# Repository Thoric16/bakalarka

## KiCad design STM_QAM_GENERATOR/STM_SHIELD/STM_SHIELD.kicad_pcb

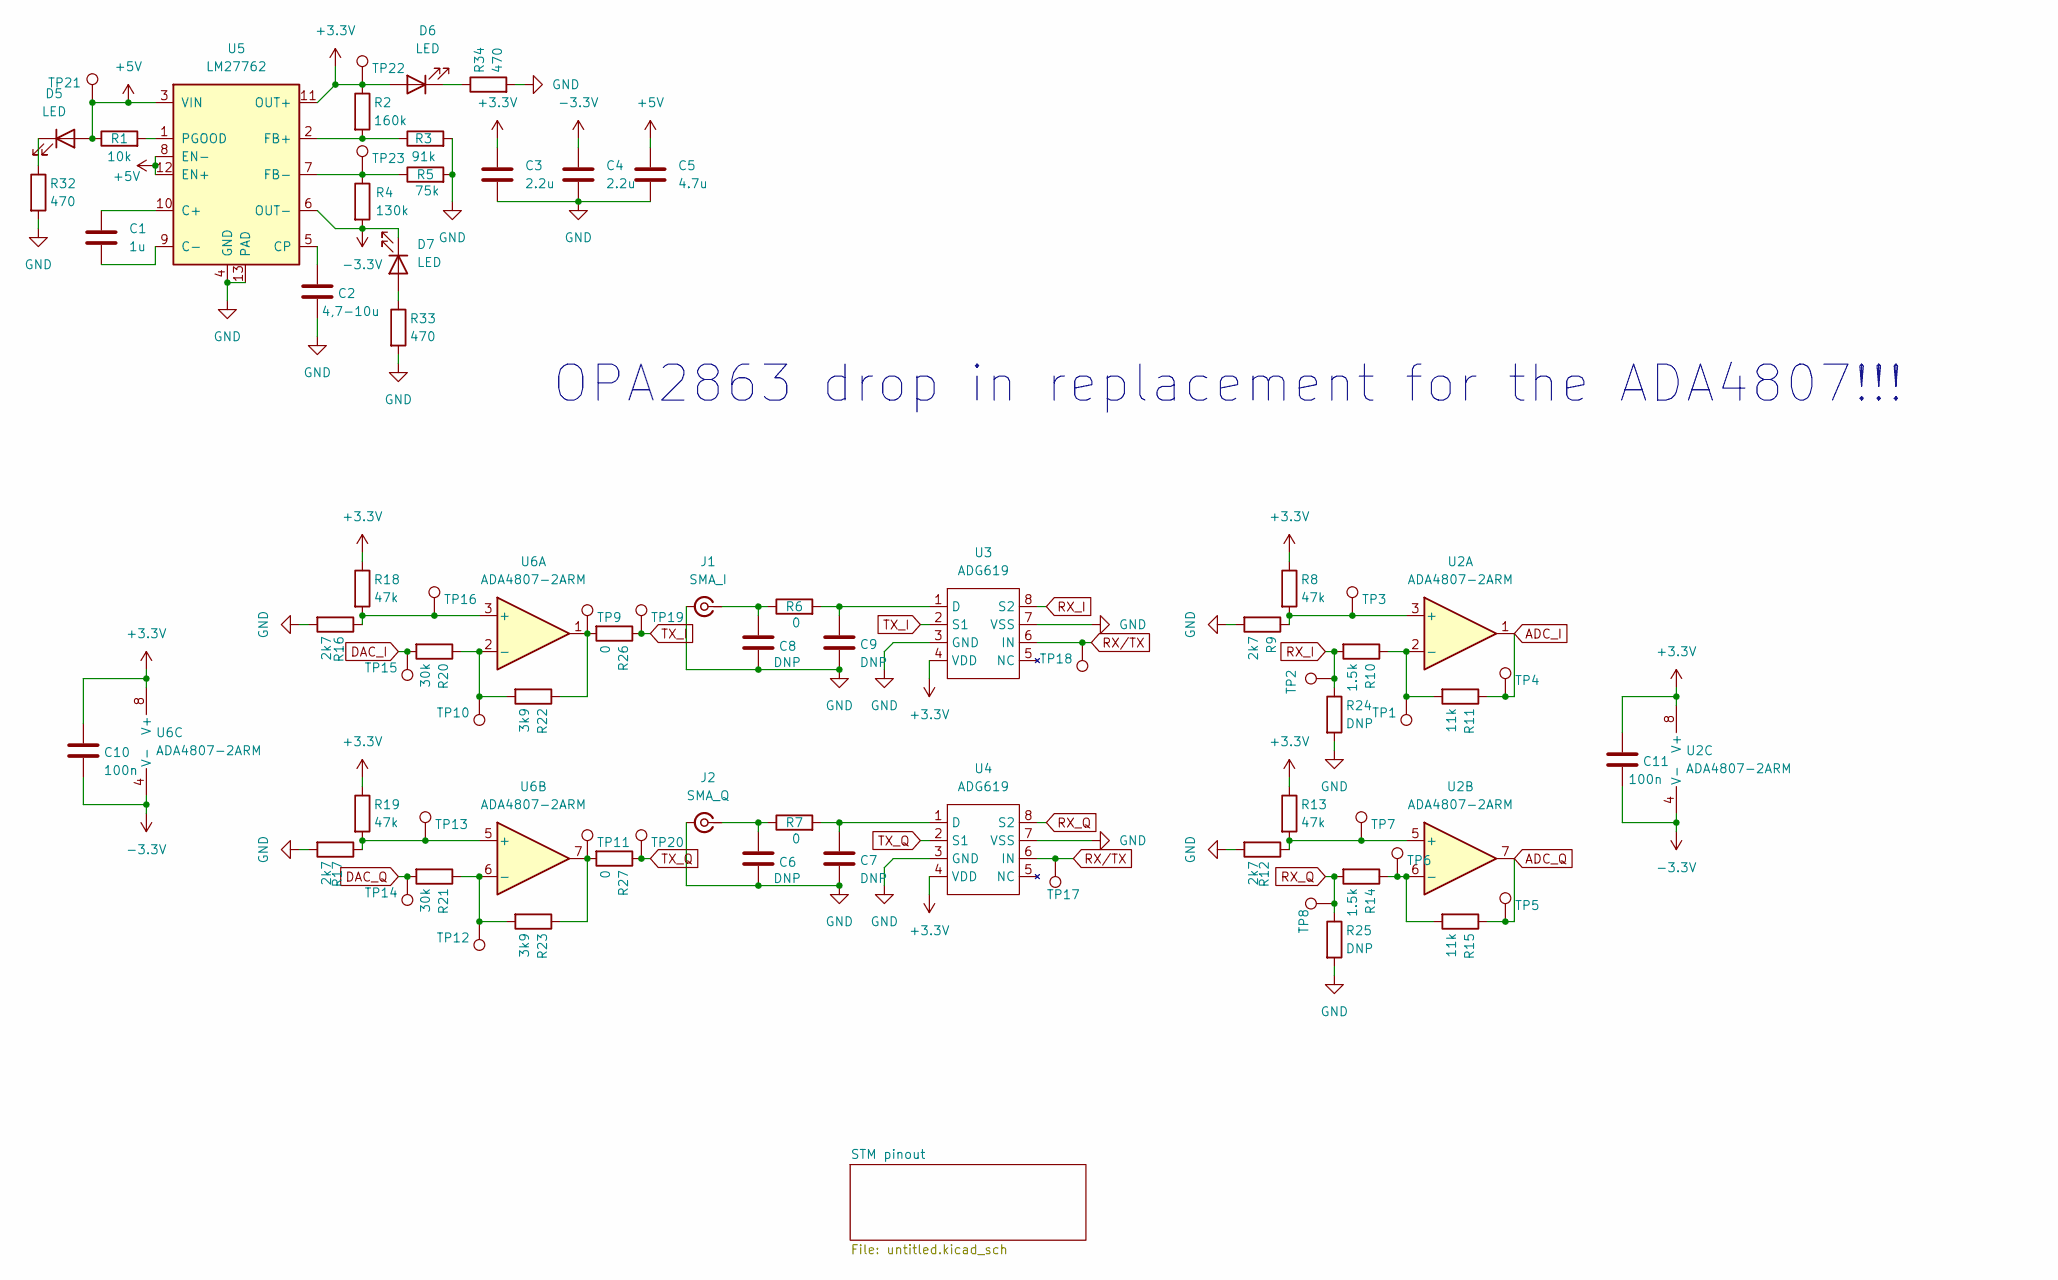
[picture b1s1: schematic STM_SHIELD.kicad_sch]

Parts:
C1: 1u; C_0603_1608Metric_Pad1.08x0.95mm_HandSolder
C2: 4,7-10u; C_0603_1608Metric_Pad1.08x0.95mm_HandSolder
C3, C4: 2.2u; C_0603_1608Metric_Pad1.08x0.95mm_HandSolder
C5: 4.7u; C_0603_1608Metric_Pad1.08x0.95mm_HandSolder
C6, C7, C8, C9: DNP; C_0603_1608Metric_Pad1.08x0.95mm_HandSolder
C10, C11: 100n; C_0603_1608Metric_Pad1.08x0.95mm_HandSolder
D5, D6, D7: LED; LED_0603_1608Metric_Pad1.05x0.95mm_HandSolder
J1: SMA_I; SMA_Samtec_SMA-J-P-H-ST-EM1_EdgeMount
J2: SMA_Q; SMA_Samtec_SMA-J-P-H-ST-EM1_EdgeMount
R1: 10k; R_0603_1608Metric_Pad0.98x0.95mm_HandSolder
R2: 160k; R_0603_1608Metric_Pad0.98x0.95mm_HandSolder
R3: 91k; R_0603_1608Metric_Pad0.98x0.95mm_HandSolder
R4: 130k; R_0603_1608Metric_Pad0.98x0.95mm_HandSolder
R5: 75k; R_0603_1608Metric_Pad0.98x0.95mm_HandSolder
R6, R7, R26, R27: 0; R_0603_1608Metric_Pad0.98x0.95mm_HandSolder
R8, R13, R18, R19: 47k; R_0603_1608Metric_Pad0.98x0.95mm_HandSolder
R9, R12, R16, R17: 2k7; R_0603_1608Metric_Pad0.98x0.95mm_HandSolder
R10, R14: 1.5k; R_0603_1608Metric_Pad0.98x0.95mm_HandSolder
R11, R15: 11k; R_0603_1608Metric_Pad0.98x0.95mm_HandSolder
R20, R21: 30k; R_0603_1608Metric_Pad0.98x0.95mm_HandSolder
R22, R23: 3k9; R_0603_1608Metric_Pad0.98x0.95mm_HandSolder
R24, R25: DNP; R_0603_1608Metric_Pad0.98x0.95mm_HandSolder
R32, R33, R34: 470; R_0603_1608Metric_Pad0.98x0.95mm_HandSolder
TP1, TP2, TP3, TP4, TP5, TP6, TP7, TP8, TP9, TP10, TP11, TP12, TP13, TP14, TP15, TP16, TP17, TP18, TP19, TP20, TP21, TP22, TP23: TestPoint; TestPoint_Pad_D1.0mm
U2, U6: ADA4807-2ARM; MSOP-8_3x3mm_P0.65mm
U3, U4: ADG619; MSOP-8_3x3mm_P0.65mm
U5: LM27762; WSON-12-1EP_3x2mm_P0.5mm_EP1x2.65_ThermalVias

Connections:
+3.3V: C3.2, C10.2, C11.2, D6.2 (A), R2.1, R8.1, R13.1, R18.1, R19.1, TP22.1, U2.8 (V+), U3.4 (VDD), U4.4 (VDD), U5.11 (OUT+), U6.8 (V+)
+5V: C5.2, D5.2 (A), R1.1, TP21.1, U5.3 (VIN), U5.8 (EN-), U5.12 (EN+); also elsewhere on the board
-3.3V: C4.2, C10.1, C11.1, D7.1 (K), R4.2, U2.4 (V-), U5.6 (OUT-), U6.4 (V-)
ADC_I: R11.1, TP4.1, U2.1; also elsewhere on the board
ADC_Q: R15.1, TP5.1, U2.7; also elsewhere on the board
DAC_I: R20.2, TP15.1; also elsewhere on the board
DAC_Q: R21.2, TP14.1; also elsewhere on the board
GND: C2.1, C3.1, C4.1, C5.1, C6.1, C7.1, C8.1, C9.1, J1.2 (Ext), J2.2 (Ext), R3.2, R5.2, R9.2, R12.2, R16.2, R17.2, R24.2, R25.2, R32.2, R33.2, R34.2, U3.3 (GND), U3.7 (VSS), U4.3 (GND), U4.7 (VSS), U5.4 (GND), U5.13 (PAD); also elsewhere on the board
unnamed: D5.1 (K), R32.1
unnamed: D6.1 (K), R34.1
unnamed: D7.2 (A), R33.1
unnamed: C8.2, J1.1 (In), R6.1
unnamed: C6.2, J2.1 (In), R7.1
unnamed: R22.1, R26.2, TP9.1, U6.1
unnamed: R23.1, R27.2, TP11.1, U6.7
unnamed: R8.2, R9.1, TP3.1, U2.3 (+)
unnamed: R10.1, R11.2, TP1.1, U2.2 (-)
unnamed: R12.1, R13.2, TP7.1, U2.5 (+)
unnamed: R14.1, R15.2, TP6.1, U2.6 (-)
unnamed: C9.2, R6.2, U3.1 (D)
unnamed: C7.2, R7.2, U4.1 (D)
unnamed: C1.2, U5.10 (C+)
unnamed: C1.1, U5.9 (C-)
unnamed: C2.2, U5.5 (CP)
unnamed: R2.2, R3.1, U5.2 (FB+)
unnamed: R4.1, R5.1, TP23.1, U5.7 (FB-)
unnamed: R1.2, U5.1 (PGOOD)
unnamed: R16.1, R18.2, TP16.1, U6.3 (+)
unnamed: R20.1, R22.2, TP10.1, U6.2 (-)
unnamed: R17.1, R19.2, TP13.1, U6.5 (+)
unnamed: R21.1, R23.2, TP12.1, U6.6 (-)
RX_I: R10.2, R24.1, TP2.1, U3.8 (S2)
RX_Q: R14.2, R25.1, TP8.1, U4.8 (S2)
RX/TX: TP17.1, TP18.1, U3.6 (IN), U4.6 (IN); also elsewhere on the board
TX_I: R26.1, TP19.1, U3.2 (S1)
TX_Q: R27.1, TP20.1, U4.2 (S1)

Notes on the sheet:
OPA2863 drop in replacement for the ADA4807!!!

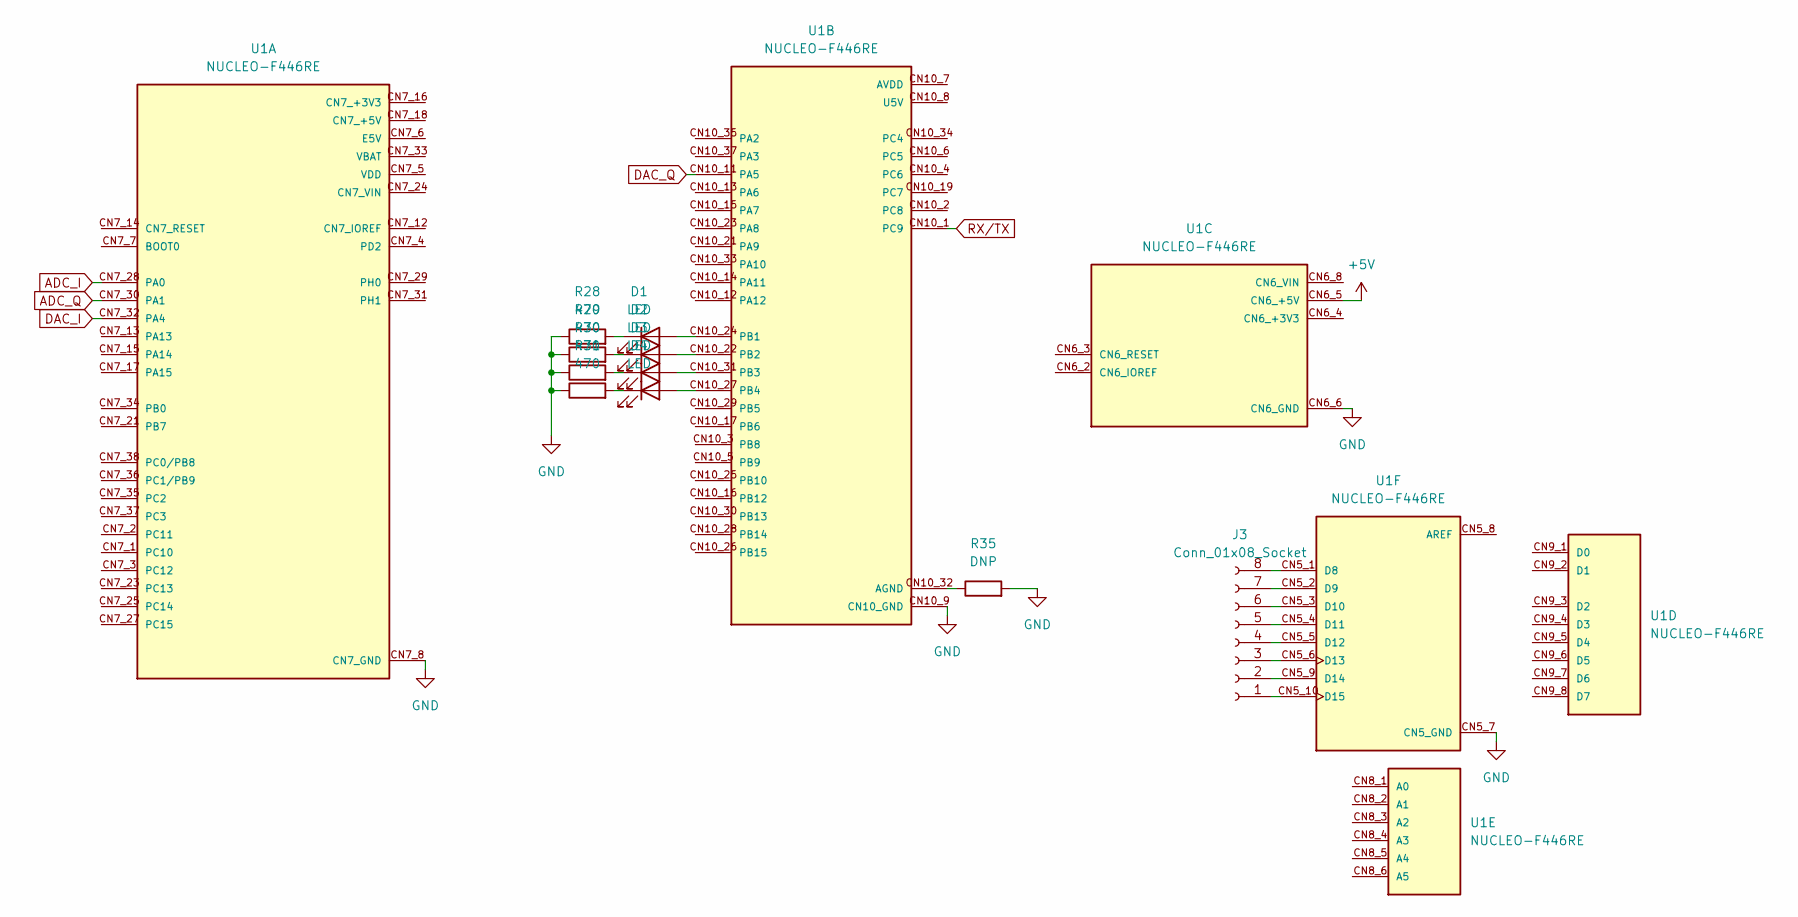
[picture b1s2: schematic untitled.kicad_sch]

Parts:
D1, D2, D3, D4: LED; LED_0603_1608Metric_Pad1.05x0.95mm_HandSolder
J3: Conn_01x08_Socket; PinSocket_1x08_P2.54mm_Vertical
R28, R29, R30, R31: 470; R_0603_1608Metric_Pad0.98x0.95mm_HandSolder
R35: DNP; R_0603_1608Metric_Pad0.98x0.95mm_HandSolder
U1: NUCLEO-F446RE; MODULE_NUCLEO-F446RE; PARTREV 13

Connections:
+5V: U1.CN6_5 (CN6_+5V); also elsewhere on the board
ADC_I: U1.CN7_28 (PA0); also elsewhere on the board
ADC_Q: U1.CN7_30 (PA1); also elsewhere on the board
DAC_I: U1.CN7_32 (PA4); also elsewhere on the board
DAC_Q: U1.CN10_11 (PA5); also elsewhere on the board
GND: R28.1, R29.1, R30.1, R31.1, R35.2, U1.CN5_7 (CN5_GND), U1.CN6_6 (CN6_GND), U1.CN6_7 (CN6_GND), U1.CN7_8 (CN7_GND), U1.CN7_19 (CN7_GND), U1.CN7_20 (CN7_GND), U1.CN7_22 (CN7_GND), U1.CN10_9 (CN10_GND), U1.CN10_20 (CN10_GND); also elsewhere on the board
unnamed: D1.2 (A), U1.CN10_24 (PB1)
unnamed: D1.1 (K), R28.2
unnamed: D2.2 (A), U1.CN10_22 (PB2)
unnamed: D2.1 (K), R29.2
unnamed: D3.2 (A), U1.CN10_31 (PB3)
unnamed: D3.1 (K), R30.2
unnamed: D4.2 (A), U1.CN10_27 (PB4)
unnamed: D4.1 (K), R31.2
unnamed: J3.1, U1.CN5_10 (D15)
unnamed: J3.2, U1.CN5_9 (D14)
unnamed: J3.3, U1.CN5_6 (D13)
unnamed: J3.4, U1.CN5_5 (D12)
unnamed: J3.5, U1.CN5_4 (D11)
unnamed: J3.6, U1.CN5_3 (D10)
unnamed: J3.7, U1.CN5_2 (D9)
unnamed: J3.8, U1.CN5_1 (D8)
unnamed: R35.1, U1.CN10_32 (AGND)
RX/TX: U1.CN10_1 (PC9); also elsewhere on the board

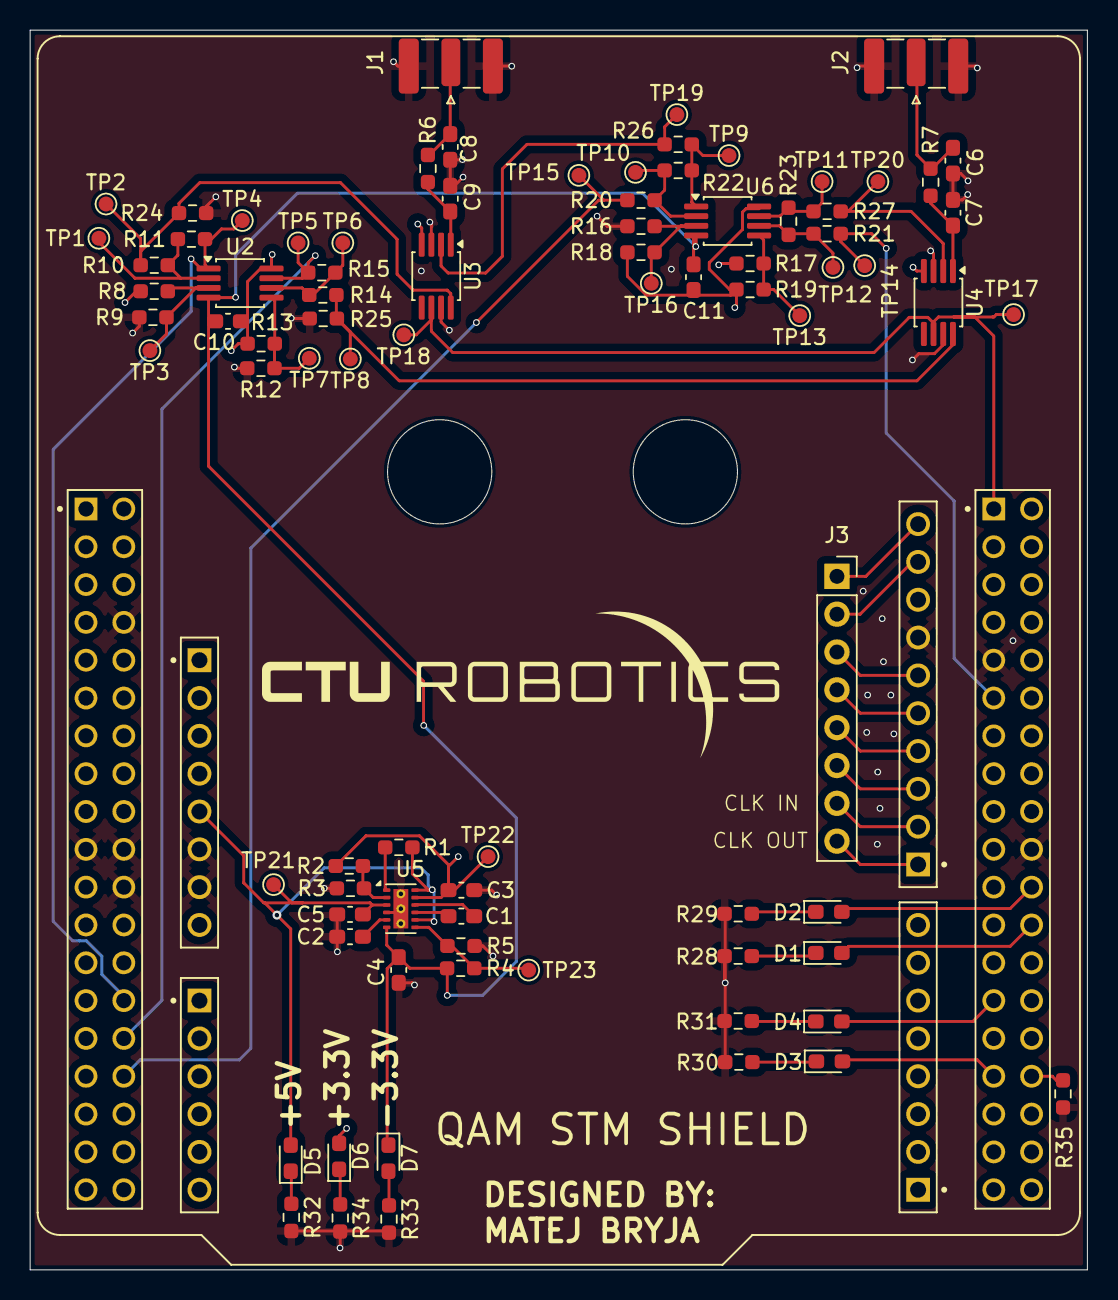
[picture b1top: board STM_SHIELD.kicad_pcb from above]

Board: 4 copper layers, 71.0 x 83.2 mm, 85 parts (0 on the bottom side), 53 nets.

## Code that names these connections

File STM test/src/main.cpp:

#include <Arduino.h>
#include <HardwareTimer.h>

constexpr uint8_t DAC_I_PIN = PA4;
constexpr uint8_t DAC_Q_PIN = PA5;
constexpr uint8_t ADC_I_PIN = PA0;
constexpr uint8_t ADC_Q_PIN = PA1;
constexpr uint8_t TX_CLOCK_PIN = D8;
constexpr uint8_t RX_CLOCK_PIN = D9;
constexpr uint8_t TX_MODE_PIN = PB1;
constexpr uint8_t RX_MODE_PIN = PB2;
constexpr uint8_t USER_BUTTON_PIN = PC13;
constexpr uint16_t DAC_MAX = 4095;
constexpr uint32_t SYMBOL_PERIOD_US = 1000;
constexpr uint32_t CLOCK_FREQUENCY_HZ = 1000000UL / SYMBOL_PERIOD_US;
constexpr uint32_t BUTTON_DEBOUNCE_MS = 50;
constexpr uint32_t LONG_PRESS_MS = 1500;
constexpr float ADC_REFERENCE_VOLTAGE = 3.3f;
constexpr uint8_t RX_PACKET_HEADER = 0xA5;
constexpr uint16_t RX_BUFFER_SIZE = 512;

struct Modulation {
  const char *name;
  uint16_t order;
  uint8_t bitsPerAxis;
};

const Modulation modulations[] = {
  {"QPSK", 4, 1},
  {"16-QAM", 16, 2},
  {"64-QAM", 64, 3},
  {"256-QAM", 256, 4},
  {"1024-QAM", 1024, 5},
  {"4096-QAM", 4096, 6}
};

constexpr size_t MODULATION_COUNT = sizeof(modulations) / sizeof(modulations[0]);
size_t modulationIndex = 0;
uint16_t symbolIndex = 0;
bool stableButtonState = HIGH;
bool candidateButtonState = HIGH;
uint32_t buttonStateChangedAt = 0;
uint32_t buttonPressStart = 0;
bool longPressHandled = false;
bool receiverMode = false;
struct RxSample {
  uint16_t i;
  uint16_t q;
};

volatile RxSample rxBuffer[RX_BUFFER_SIZE];
volatile uint16_t rxBufferHead = 0;
volatile uint16_t rxBufferTail = 0;
volatile uint32_t rxDroppedSamples = 0;
HardwareTimer *txClockTimer = nullptr;

uint16_t axisLevel(uint16_t axisIndex, uint8_t bitsPerAxis) {
  const uint16_t axisLevels = 1U << bitsPerAxis;
  if (axisLevels == 1) {
    return DAC_MAX / 2;
  }
  return static_cast<uint16_t>((static_cast<uint32_t>(axisIndex) * DAC_MAX) / (axisLevels - 1));
}

void printModulationInfo() {
  const Modulation &modulation = modulations[modulationIndex];
  Serial.println();
  Serial.print("--- ");
  Serial.print(receiverMode ? "RX" : "TX");
  Serial.println(" mode ---");
  Serial.print("Current modulation: ");
  Serial.println(modulation.name);
  Serial.print("States: ");
  Serial.println(modulation.order);
  Serial.print("Bits per symbol: ");
  Serial.println(2 * modulation.bitsPerAxis);
  Serial.println("DAC pins: I=PA4, Q=PA5, range=0..4095");
  Serial.println("ADC pins: I=PA0, Q=PA1");
  Serial.println("Clock pins: TX=D8, RX=D9");
  Serial.println("RX samples ADC values on each rising clock edge.");
  Serial.println("Short press: next modulation. Hold 1.5 s: toggle TX/RX.");
}

void receiveClockEdge() {
  const uint16_t nextHead = (rxBufferHead + 1) % RX_BUFFER_SIZE;
  if (nextHead == rxBufferTail) {
    rxDroppedSamples++;
    return;
  }

  rxBuffer[rxBufferHead].i = analogRead(ADC_I_PIN);
  rxBuffer[rxBufferHead].q = analogRead(ADC_Q_PIN);
  rxBufferHead = nextHead;
}

void setMode(bool newReceiverMode) {
  receiverMode = newReceiverMode;
  symbolIndex = 0;
  digitalWrite(TX_MODE_PIN, receiverMode ? LOW : HIGH);
  digitalWrite(RX_MODE_PIN, receiverMode ? HIGH : LOW);
  noInterrupts();
  rxBufferHead = 0;
  rxBufferTail = 0;
  rxDroppedSamples = 0;
  interrupts();

  if (receiverMode) {
    txClockTimer->pause();
    detachInterrupt(digitalPinToInterrupt(RX_CLOCK_PIN));
    pinMode(TX_CLOCK_PIN, INPUT);
    pinMode(RX_CLOCK_PIN, INPUT);
    attachInterrupt(digitalPinToInterrupt(RX_CLOCK_PIN), receiveClockEdge, RISING);
  } else {
    detachInterrupt(digitalPinToInterrupt(RX_CLOCK_PIN));
    pinMode(RX_CLOCK_PIN, INPUT);
    txClockTimer->setMode(1, TIMER_OUTPUT_COMPARE_PWM1, TX_CLOCK_PIN);
    txClockTimer->setCount(0);
    txClockTimer->resume();
  }

  printModulationInfo();
}

void streamReceivedSamples() {
  uint8_t streamedSamples = 0;
  while (streamedSamples < 32) {
    uint16_t currentI;
    uint16_t currentQ;

    noInterrupts();
    if (rxBufferTail == rxBufferHead) {
      interrupts();
      return;
    }
    currentI = rxBuffer[rxBufferTail].i;
    streamedSamples++;
    currentQ = rxBuffer[rxBufferTail].q;
    rxBufferTail = (rxBufferTail + 1) % RX_BUFFER_SIZE;
    interrupts();

    const uint8_t packet[] = {
        RX_PACKET_HEADER,
        static_cast<uint8_t>(currentI & 0xFF),
        static_cast<uint8_t>(currentI >> 8),
        static_cast<uint8_t>(currentQ & 0xFF),
        static_cast<uint8_t>(currentQ >> 8)};
    Serial.write(packet, sizeof(packet));
  }
}

void processSerialCommands() {
  static char command[16];
  static uint8_t commandLength = 0;

  while (Serial.available() > 0) {
    const char character = static_cast<char>(Serial.read());
    if (character == '\n' || character == '\r') {
      command[commandLength] = '\0';
      if (strcmp(command, "RX") == 0) {
        setMode(true);
      } else if (strcmp(command, "TX") == 0) {
        setMode(false);
      } else if (strcmp(command, "NEXT") == 0 && !receiverMode) {
        modulationIndex = (modulationIndex + 1) % MODULATION_COUNT;
        symbolIndex = 0;
        printModulationInfo();
      } else if (strncmp(command, "MOD ", 4) == 0 && !receiverMode) {
        const int requestedIndex = atoi(command + 4);
        if (requestedIndex >= 0 && requestedIndex < static_cast<int>(MODULATION_COUNT)) {
          modulationIndex = requestedIndex;
          symbolIndex = 0;
          printModulationInfo();
        }
      } else if (strcmp(command, "DROPPED") == 0) {
        Serial.print("DROPPED ");
        Serial.println(rxDroppedSamples);
      }
      commandLength = 0;
    } else if (commandLength < sizeof(command) - 1) {
      command[commandLength++] = character;
    }
  }
}

void checkButton() {
  const bool buttonState = digitalRead(USER_BUTTON_PIN);
  const uint32_t now = millis();

  if (buttonState != candidateButtonState) {
    candidateButtonState = buttonState;
    buttonStateChangedAt = now;
  }

  if (candidateButtonState != stableButtonState &&
      now - buttonStateChangedAt >= BUTTON_DEBOUNCE_MS) {
    stableButtonState = candidateButtonState;
    if (stableButtonState == LOW) {
      buttonPressStart = now;
      longPressHandled = false;
      Serial.println("Button pressed: hold for 1.5 s to toggle TX/RX.");
    } else {
      const uint32_t pressDuration = now - buttonPressStart;
      if (!longPressHandled && pressDuration < LONG_PRESS_MS && !receiverMode) {
        modulationIndex = (modulationIndex + 1) % MODULATION_COUNT;
        symbolIndex = 0;
        printModulationInfo();
      }
    }
  }

  if (stableButtonState == LOW && !longPressHandled &&
      now - buttonPressStart >= LONG_PRESS_MS) {
    longPressHandled = true;
    Serial.println("Long press detected: switching mode.");
    setMode(!receiverMode);
  }
}

void transmitSymbolOnClockFallingEdge() {
  const Modulation &modulation = modulations[modulationIndex];
  const uint16_t axisLevels = 1U << modulation.bitsPerAxis;
  const uint16_t iIndex = symbolIndex % axisLevels;
  const uint16_t qIndex = symbolIndex / axisLevels;

  analogWrite(DAC_I_PIN, axisLevel(iIndex, modulation.bitsPerAxis));
  analogWrite(DAC_Q_PIN, axisLevel(qIndex, modulation.bitsPerAxis));

  symbolIndex++;
  if (symbolIndex >= modulation.order) {
    symbolIndex = 0;
  }
}

void setup() {
  Serial.begin(115200);
  pinMode(DAC_I_PIN, OUTPUT);
  pinMode(DAC_Q_PIN, OUTPUT);
  pinMode(ADC_I_PIN, INPUT_ANALOG);
  pinMode(ADC_Q_PIN, INPUT_ANALOG);
  pinMode(TX_MODE_PIN, OUTPUT);
  pinMode(RX_MODE_PIN, OUTPUT);
  pinMode(USER_BUTTON_PIN, INPUT_PULLUP);
  pinMode(RX_CLOCK_PIN, INPUT);
  stableButtonState = digitalRead(USER_BUTTON_PIN);
  candidateButtonState = stableButtonState;
  buttonStateChangedAt = millis();
  analogWriteResolution(12);
  analogReadResolution(12);
  digitalWrite(TX_MODE_PIN, HIGH);
  digitalWrite(RX_MODE_PIN, LOW);

  txClockTimer = new HardwareTimer(TIM4);
  txClockTimer->setOverflow(CLOCK_FREQUENCY_HZ, HERTZ_FORMAT);
  txClockTimer->setCaptureCompare(1, 50, PERCENT_COMPARE_FORMAT);
  txClockTimer->setMode(1, TIMER_OUTPUT_COMPARE_PWM1, TX_CLOCK_PIN);
  txClockTimer->attachInterrupt(1, transmitSymbolOnClockFallingEdge);

  analogWrite(DAC_I_PIN, axisLevel(0, modulations[modulationIndex].bitsPerAxis));
  analogWrite(DAC_Q_PIN, axisLevel(0, modulations[modulationIndex].bitsPerAxis));
  printModulationInfo();
  txClockTimer->setCount(0);
  txClockTimer->resume();
}

void loop() {
  processSerialCommands();
  checkButton();

  if (receiverMode) {
    streamReceivedSamples();
    return;
  }

}

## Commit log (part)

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2026-06-02 Frequency limits for HMC513
2026-06-04 Create notes
    creation of notes file
2026-06-04 Updated notes
2026-06-06 nucleo-f446re -STM32F446RE Datasheet added
2026-06-06 hmc513 and hmc521 datasheets
2026-06-06 preliminary schematic added
2026-06-07 Preliminary diagram KiCad
2026-06-07 diagram.png
2026-06-08 Update notes
2026-06-24 added datasheet for hmc1056
2026-06-24 added Datasheets/hmc1056 (1).pdf
2026-06-30 new file: Datasheets/hmc451lp3.pdf
